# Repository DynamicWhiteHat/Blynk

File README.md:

# Blynk
A feature-rich LED controller

> [!NOTE]
> This board runs on [WLED firmware](https://kno.wled.ge/)

## Features:
- Powered by an ESP32 S3
- ICS-43434 microphone
- Plus line-in with ES7243
- Low-profile PIR for motion detection
- IR receiver with custom remote control
- BH1750 ambient light sensor
- Full RGBW CCT support
- Reverse polarity protection and automatic supply switching

## Image Gallery:
<table align="center">
  <tr>
    <td align="center">
      
    </td>
    <td align="center">
      
    </td>
  </tr>
  <tr>
    <td align="center" colspan="2">
      
    </td>
  </tr>
</table>

## Why I Designed This Project:
I began this project because I am getting a new large table built in my room and would love some LED lighting under it. I decided to make myself an LED controller with a lot of features. Most importantly, I wanted to have it be compatible with Alexa to match the other lights in my room. After a quick search, I found that the WLED firmware accomplishes all that I want: it is feature-rich, Alexa compatible, and supports custom ESP32 boards. And so, I embarked on a quest to make the most feature-packed LED controller to exist.

## Schematics And PCBs:
<table align="center">
  <tr>
    <td align="center" colspan="2">
      
    </td>
  </tr>
  <tr>
     <td align="center">
      
    </td>
    <td align="center">
      
    </td>
  </tr>
</table>

## Usage:
Follow the instructions on the [WLED getting started page](https://kno.wled.ge/basics/getting-started/) after assembling your PCB to get it running.

## BOM:
|Part                       |Quantity       |Price              |Link                                                                                  |                 |        |   |                                            |
|---------------------------|---------------|-------------------|--------------------------------------------------------------------------------------|-----------------------|--------------|---------|--------------------------------------------------|
|PCB+Stencil                |1              |$24.07             |JLCPCB Quote                                                                          |                       |              |         |                                                  |
|PCB Parts                  |1              |$56.25             |See Below                                                                             |                       |              |         |                                                  |
|LED Strip                  |1              |$6.96              |https://www.aliexpress.us/item/3256808756097464.html                                  |                       |              |         |                                                  |
|M2 Screws                  |1              |$5.22              |https://www.aliexpress.us/item/3256807092650644.html                                  |                       |              |         |                                                  |
|Power Supply               |1              |$13.94             |https://www.amazon.com/TOBWOLF-100V-240V-Transformer-Switching-Converter/dp/B0B1DGBVKB|                       |              |         |                                                  |
|PIR                        |1              |$3.48              |https://www.aliexpress.us/item/3256812509957711.html                                  |                       |              |         |                                                  |
|                           |Total          |$109.92            |                                                                                      |                       |              |         |                                                  |
|LCSC BOM                   |               |                   |                                                                                      |                       |              |         |                                                  |
|Description                |Quantity Needed|Mrf#               |Minimum Order Qty.                                                                    |Unit Price(USD)        |Ext.Price(USD)|LCSC#    |Product Link                                      |
|0.1uF                      |6              |CC0603KRX7R9BB104  |50                                                                                    |0.0186                 |0.93          |C14663   |https://www.lcsc.com/product-detail/C14663.html   |
|100K                       |1              |0603WAF1003T5E     |100                                                                                   |0.0068                 |0.68          |C25803   |https://www.lcsc.com/product-detail/C25803.html   |
|100R                       |3              |0603WAF1000T5E     |100                                                                                   |0.0222                 |2.22          |C22775   |https://www.lcsc.com/product-detail/C22775.html   |
|100nF                      |4              |CC0603KRX7R9BB104  |50                                                                                    |0.0186                 |0.93          |C14663   |https://www.lcsc.com/product-detail/C14663.html   |
|10K                        |8              |0603WAF1002T5E     |100                                                                                   |0.0085                 |0.85          |C25804   |https://www.lcsc.com/product-detail/C25804.html   |
|10uF                       |1              |CL10A106MA8NRNC    |20                                                                                    |0.0841                 |1.68          |C96446   |https://www.lcsc.com/product-detail/C96446.html   |
|150R                       |1              |0603WAF1500T5E     |100                                                                                   |0.0087                 |0.87          |C22808   |https://www.lcsc.com/product-detail/C22808.html   |
|1K                         |1              |0603WAF1001T5E     |100                                                                                   |0.0058                 |0.58          |C21190   |https://www.lcsc.com/product-detail/C21190.html   |
|1uF                        |10             |CL10A105KB8NNNC    |50                                                                                    |0.0275                 |1.38          |C15849   |https://www.lcsc.com/product-detail/C15849.html   |
|2.2uH                      |1              |CMH160808B2R2MT    |20                                                                                    |0.0324                 |0.65          |C394950  |https://www.lcsc.com/product-detail/C394950.html  |
|20K                        |1              |0603WAF2002T5E     |100                                                                                   |0.0052                 |0.52          |C4184    |https://www.lcsc.com/product-detail/C4184.html    |
|220R                       |5              |0603WAF2200T5E     |100                                                                                   |0.0086                 |0.86          |C22962   |https://www.lcsc.com/product-detail/C22962.html   |
|22uF                       |5              |CL10A226MQ8NRNC    |20                                                                                    |0.0313                 |0.63          |C59461   |https://www.lcsc.com/product-detail/C59461.html   |
|33.2K                      |1              |0603WAF3322T5E     |100                                                                                   |0.0034                 |0.34          |C23003   |https://www.lcsc.com/product-detail/C23003.html   |
|4.7K                       |3              |0603WAF4701T5E     |100                                                                                   |0.0118                 |1.18          |C23162   |https://www.lcsc.com/product-detail/C23162.html   |
|4.7uF                      |1              |CL10A475KO8NNNC    |10                                                                                    |0.0335                 |0.34          |C19666   |https://www.lcsc.com/product-detail/C19666.html   |
|47R                        |1              |0603WAF470JT5E     |100                                                                                   |0.0075                 |0.75          |C23182   |https://www.lcsc.com/product-detail/C23182.html   |
|5.1k                       |2              |0603WAF5101T5E     |100                                                                                   |0.0038                 |0.38          |C23186   |https://www.lcsc.com/product-detail/C23186.html   |
|750 mA                     |1              |BSMD0603-075-6V    |10                                                                                    |0.0672                 |0.67          |C914092  |https://www.lcsc.com/product-detail/C914092.html  |
|8A                         |1              |BSMD2920L-1000-24V |1                                                                                     |0.634                  |0.63          |C48392676|https://www.lcsc.com/product-detail/C48392676.html|
|AO3400A                    |6              |AO3400A            |10                                                                                    |0.0849                 |0.85          |C20917   |https://www.lcsc.com/product-detail/C20917.html   |
|AOD4184A                   |1              |AOD4184A           |5                                                                                     |0.3474                 |1.74          |C99124   |https://www.lcsc.com/product-detail/C99124.html   |
|ATtiny1616-S               |1              |ATTINY1616-SN      |1                                                                                     |2.9131                 |2.91          |C614136  |https://www.lcsc.com/product-detail/C614136.html  |
|AudioPlug3                 |1              |SJ1-3523N          |1                                                                                     |0.8493                 |0.85          |C20182914|https://www.lcsc.com/product-detail/C20182914.html|
|BH1750                     |1              |BH1750FVI-TR       |1                                                                                     |0.9687                 |0.97          |C78960   |https://www.lcsc.com/product-detail/C78960.html   |
|BLM15PX121SN1D             |2              |BLM15PX121SN1D11   |50                                                                                    |0.0097                 |0.49          |C882964  |https://www.lcsc.com/product-detail/C882964.html  |
|CR2032                     |1              |BS-07-A1BJ001      |5                                                                                     |0.379                  |1.9           |C2979167 |https://www.lcsc.com/product-detail/C2979167.html |
|D                          |1              |BSD3C051V          |10                                                                                    |0.0661                 |0.66          |C151996  |https://www.lcsc.com/product-detail/C151996.html  |
|ES7243                     |1              |ES7243E            |1                                                                                     |0.5557                 |0.56          |C2929446 |https://www.lcsc.com/product-detail/C2929446.html |
|ESP32-S3-WROOM-1           |1              |ESP32-S3-WROOM-1-N8|1                                                                                     |4.91                   |4.91          |C2913198 |https://www.lcsc.com/product-detail/C2913198.html |
|ICS-43434                  |1              |ICS-43434          |1                                                                                     |3.8207                 |3.82          |C5656610 |https://www.lcsc.com/product-detail/C5656610.html |
|LM5050-1                   |1              |LM5050MK-1/NOPB    |1                                                                                     |1.1867                 |1.19          |C129323  |https://www.lcsc.com/product-detail/C129323.html  |
|SMBJ15A                    |1              |SMBJ15A            |5                                                                                     |0.0539                 |0.27          |C19077569|https://www.lcsc.com/product-detail/C19077569.html|
|SS34                       |1              |SS34               |20                                                                                    |0.0352                 |0.7           |C8678    |https://www.lcsc.com/product-detail/C8678.html    |
|SW_Push                    |2              |TS-1088-AR02016    |10                                                                                    |0.0529                 |0.53          |C720477  |https://www.lcsc.com/product-detail/C720477.html  |
|SW_Push_45deg              |12             |TS-1088-AR02016    |20                                                                                    |0.0529                 |1.06          |C720477  |https://www.lcsc.com/product-detail/C720477.html  |
|Screw_Terminal_01x02       |1              |KF126-5.0-2P       |5                                                                                     |0.0844                 |0.42          |C474900  |https://www.lcsc.com/product-detail/C474900.html  |
|TPS563201                  |1              |TPS563201DDCR      |10                                                                                    |0.0769                 |0.77          |C116592  |https://www.lcsc.com/product-detail/C116592.html  |
|TSAL4400                   |1              |TSAL4400           |5                                                                                     |0.4254                 |2.13          |C94135   |https://www.lcsc.com/product-detail/C94135.html   |
|TSOP38238                  |1              |TSOP38238          |1                                                                                     |0.7752                 |0.78          |C141632  |https://www.lcsc.com/product-detail/C141632.html  |
|USBLC6-2P6                 |1              |USBLC6-2P6         |5                                                                                     |0.2787                 |1.39          |C15999   |https://www.lcsc.com/product-detail/C15999.html   |
|USB_C_Receptacle_USB2.0_16P|1              |TYPE-C-31-M-12     |5                                                                                     |0.1716                 |0.86          |C165948  |https://www.lcsc.com/product-detail/C165948.html  |
|                           |               |                   |                                                                                      |Subtotal:              |46.83         |         |                                                  |
|                           |               |                   |                                                                                      |Shipping:              |12.76         |         |                                                  |
|                           |               |                   |                                                                                      |Total (after discount):|$56.25        |         |                                                  |

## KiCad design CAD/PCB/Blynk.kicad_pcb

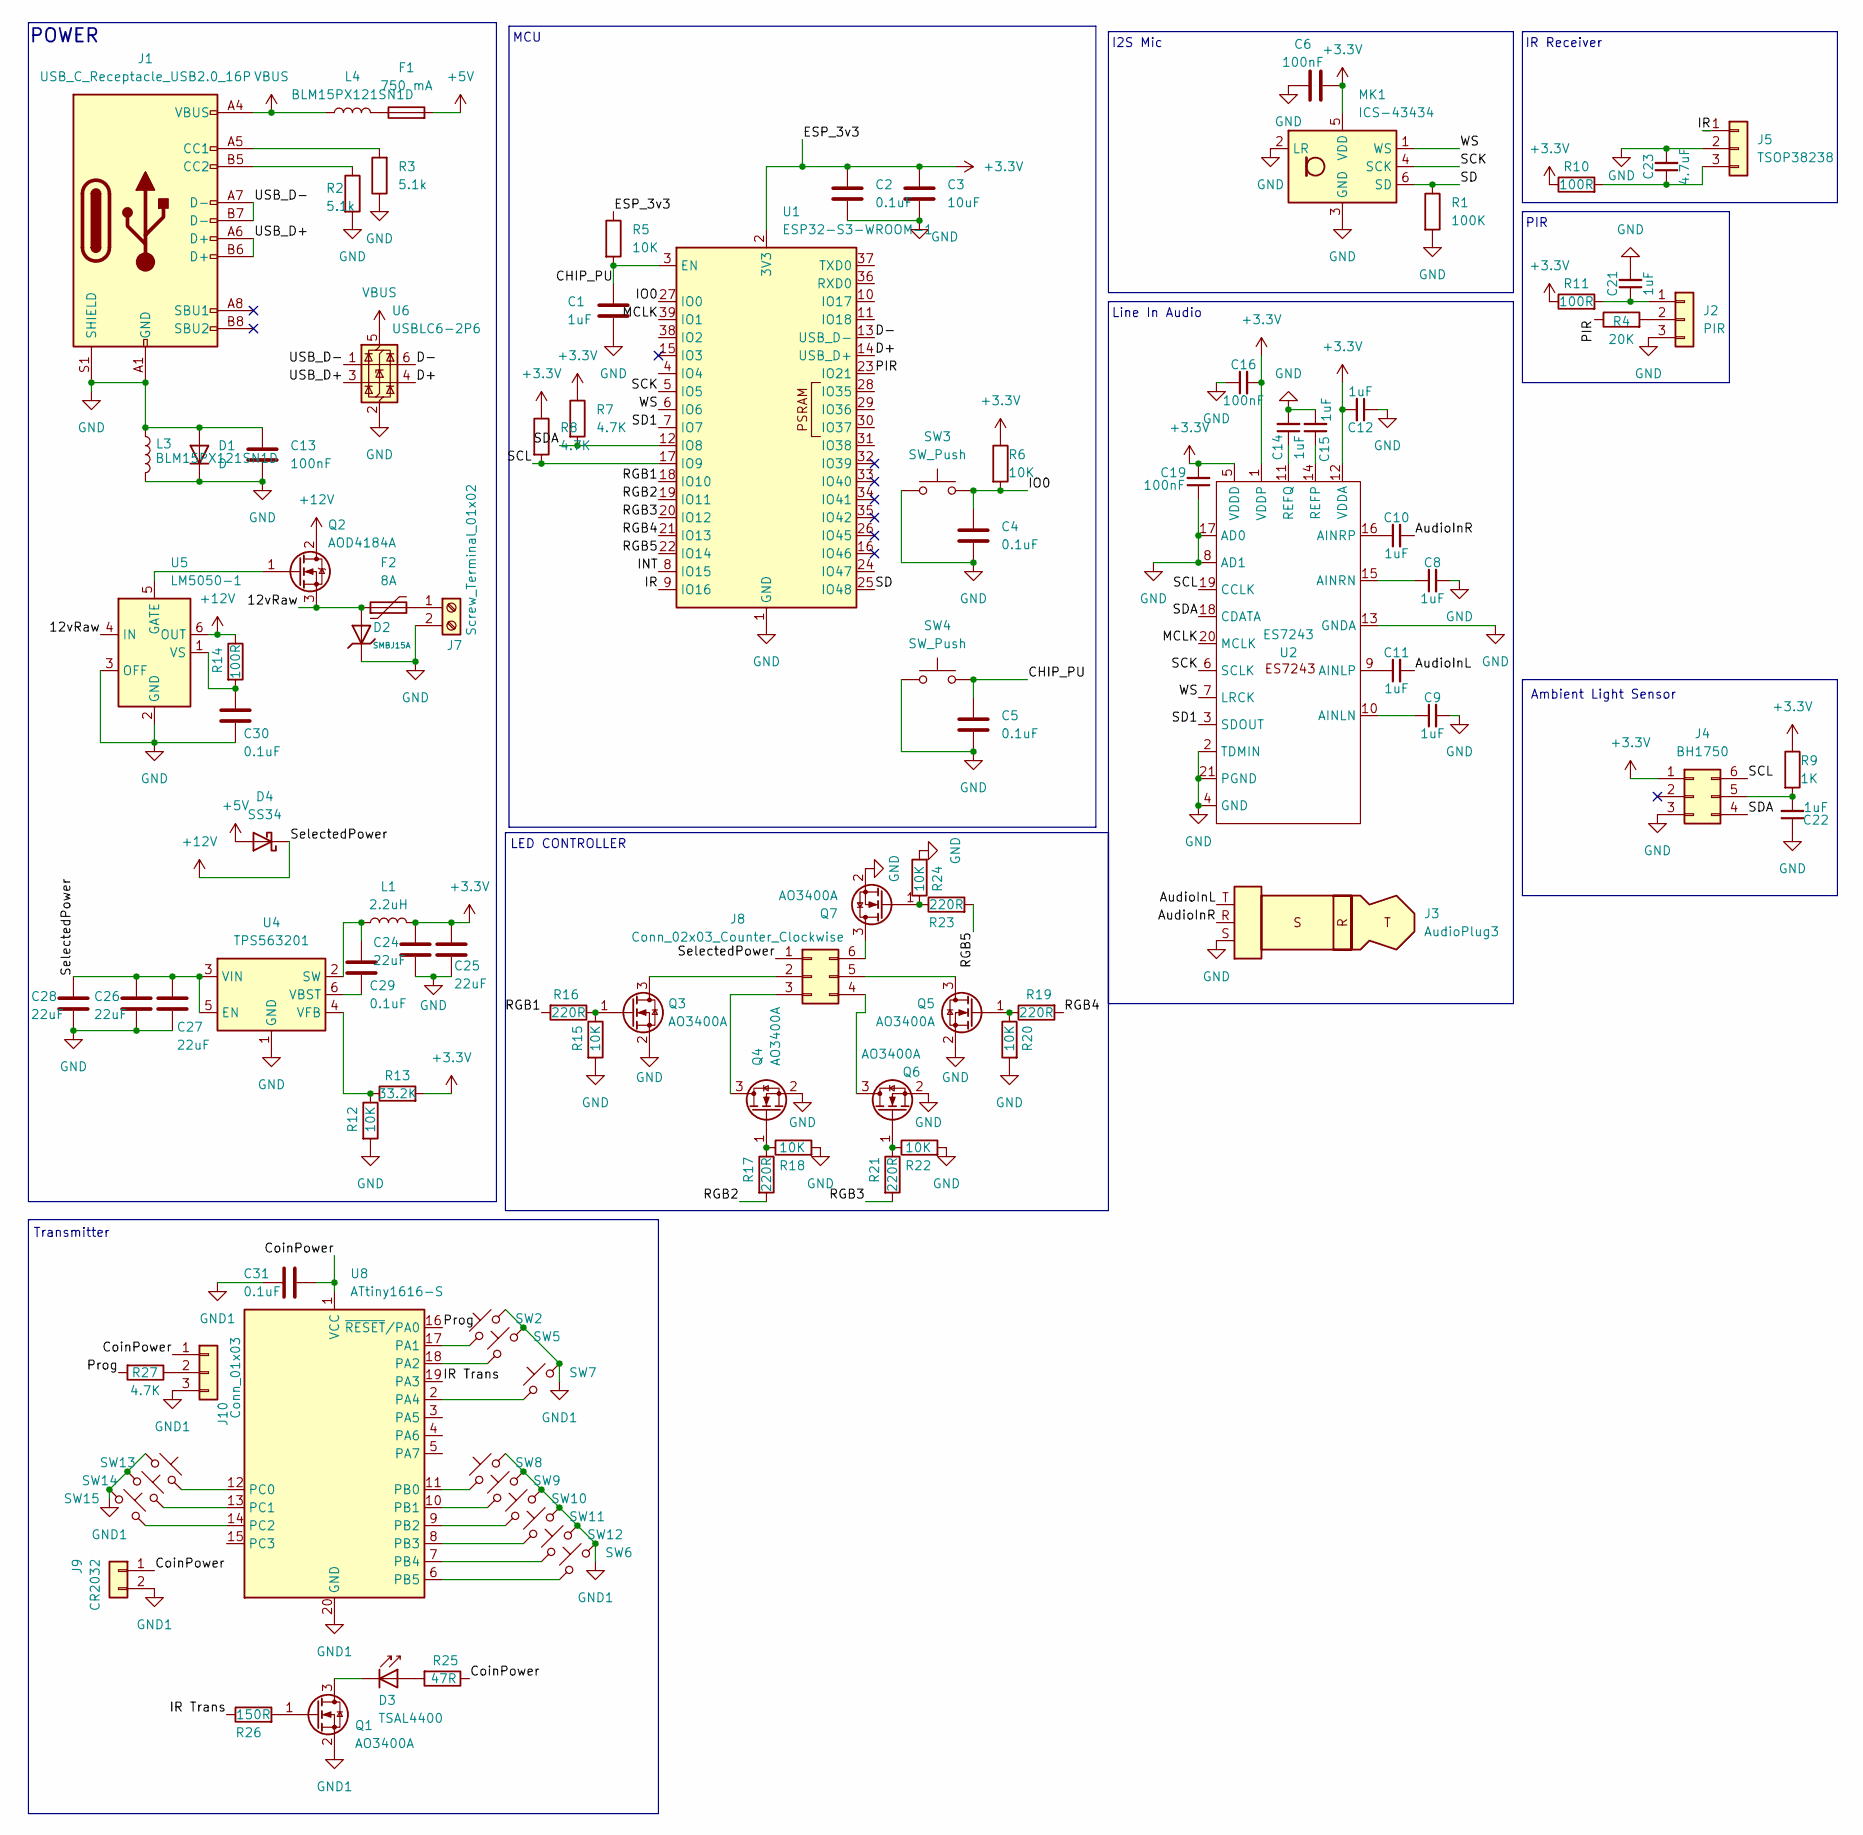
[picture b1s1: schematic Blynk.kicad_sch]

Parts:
C1, C8, C9, C10, C11, C12, C14, C15, C21, C22: 1uF; C_0603_1608Metric
C2, C4, C5, C29, C30, C31: 0.1uF; C_0603_1608Metric
C3: 10uF; C_0603_1608Metric
C6, C13, C16, C19: 100nF; C_0603_1608Metric
C23: 4.7uF; C_0603_1608Metric
C24, C25, C26, C27, C28: 22uF; C_0603_1608Metric
D1: D; D_SOD-323
D2: SMBJ15A; D_SMB; Part SMBJ15A; LCSC C19077569
D3: TSAL4400; LED_D3.0mm_IRBlack
D4: SS34; D_SMA
F1: 750 mA; Fuse_0603_1608Metric
F2: 8A; Fuse_2920_7451Metric
J1: USB_C_Receptacle_USB2.0_16P; USB_C_Receptacle_HRO_TYPE-C-31-M-12
J2: PIR; PinHeader_1x03_P2.54mm_Vertical
J3: AudioPlug3; Jack_3.5mm_CUI_SJ1-3523N_Horizontal
J4: BH1750; XDCR_BH1750FVI-TR
J5: TSOP38238; PinHeader_1x03_P2.54mm_Vertical
J7: Screw_Terminal_01x02; Altech_AK100_1x02_P5.00mm
J8: Conn_02x03_Counter_Clockwise; PinHeader_1x06_P2.54mm_Vertical
J9: CR2032; BatteryHolder_MYOUNG_BS-07-A1BJ001_CR2032
J10: Conn_01x03; PinHeader_1x03_P1.27mm_Vertical
L1: 2.2uH; L_0603_1608Metric
L3, L4: BLM15PX121SN1D; L_0402_1005Metric
MK1: ICS-43434; InvenSense_ICS-43434-6_3.5x2.65mm
Q1, Q3, Q4, Q5, Q6, Q7: AO3400A; SOT-23
Q2: AOD4184A; TO-252-2
R1: 100K; R_0603_1608Metric
R2, R3: 5.1k; R_0603_1608Metric
R4: 20K; R_0603_1608Metric
R5, R6, R12, R15, R18, R20, R22, R24: 10K; R_0603_1608Metric
R7, R8, R27: 4.7K; R_0603_1608Metric
R9: 1K; R_0603_1608Metric
R10, R11, R14: 100R; R_0603_1608Metric
R13: 33.2K; R_0603_1608Metric
R16, R17, R19, R21, R23: 220R; R_0603_1608Metric
R25: 47R; R_0603_1608Metric
R26: 150R; R_0603_1608Metric
SW2, SW5, SW6, SW7, SW8, SW9, SW10, SW11, SW12, SW13, SW14, SW15: SW_Push_45deg; SW_TS-1088-AR02016
SW3, SW4: SW_Push; SW_TS-1088-AR02016
U1: ESP32-S3-WROOM-1
U2: ES7243; QFN-20-1EP_3x3mm_P0.4mm_EP1.65x1.65mm
U4: TPS563201; SOT-23-6
U5: LM5050-1; TSOT-23-6
U6: USBLC6-2P6; SOT-666
U8: ATtiny1616-S; SOIC-20W_7.5x12.8mm_P1.27mm

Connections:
+3.3V: C2.1, C3.1, C6.2, C12.2, C16.2, C19.2, C24.1, C25.1, J4.1, L1.2, MK1.5 (VDD), R5.1, R6.1, R7.1, R8.1, R9.1, R10.1, R11.1, R13.2, U1.2 (3V3), U2.1 (VDDP), U2.5 (VDDD), U2.12 (VDDA)
+5V: D4.2 (A), F1.2
+12V: C26.1, C27.1, C28.1, D4.1 (K), J8.1, Q2.2 (D), R14.1, U4.3 (VIN), U4.5 (EN), U5.6 (OUT)
/12vRaw: D2.2, F2.1, Q2.3 (S), U5.4 (IN)
/AudioInL: C11.2, J3.T
/AudioInR: C10.2, J3.R
/CHIP_PU: C1.1, C5.1, R5.2, SW4.2, U1.3 (EN)
/CoinPower: C31.1, J9.1, J10.1, R25.1, U8.1 (VCC)
/D+: U1.14 (USB_D+), U6.4 (I/O2)
/D-: U1.13 (USB_D-), U6.6 (I/O1)
/INT: U1.8 (IO15)
/IO0: C4.1, R6.2, SW3.2, U1.27 (IO0)
/IR: J5.1, U1.9 (IO16)
/IR Trans: R26.1, U8.19 (PA3)
/MCLK: U1.39 (IO1), U2.20 (MCLK)
/PIR: R4.1, U1.23 (IO21)
/Prog: R27.2, U8.16 (~RESET/PA0)
/RGB1: R16.2, U1.18 (IO10)
/RGB2: R17.2, U1.19 (IO11)
/RGB3: R21.2, U1.20 (IO12)
/RGB4: R19.2, U1.21 (IO13)
/RGB5: R23.2, U1.22 (IO14)
/SCK: MK1.4 (SCK), U1.5 (IO5), U2.6 (SCLK)
/SCL: J4.6, R8.2, U1.17 (IO9), U2.19 (CCLK)
/SD: MK1.6 (SD), R1.1, U1.25 (IO48)
/SD1: U1.7 (IO7), U2.3 (SDOUT)
/SDA: J4.4, R7.2, U1.12 (IO8), U2.18 (CDATA)
/USB_D+: J1.A6 (D+), J1.B6 (D+), U6.3 (I/O2)
/USB_D-: J1.A7 (D-), J1.B7 (D-), U6.1 (I/O1)
/WS: MK1.1 (WS), U1.6 (IO6), U2.7 (LRCK)
GND: C1.2, C2.2, C3.2, C4.2, C5.2, C6.1, C8.2, C9.2, C12.1, C13.1, C13.2, C14.2, C15.2, C16.1, C19.1, C21.2, C22.1, C23.2, C24.2, C25.2, C26.2, C27.2, C28.2, C30.2, D1.1 (K), D1.2 (A), D2.1, J1.A1 (GND), J1.A12 (GND), J1.B1 (GND), J1.B12 (GND), J1.S1 (SHIELD), J2.3, J3.S, J4.3, J5.2, J7.2, L3.1, L3.2, MK1.2 (LR), MK1.3 (GND), Q3.2 (S), Q4.2 (S), Q5.2 (S), Q6.2 (S), Q7.2 (S), R1.2, R2.2, R3.1, R12.2, R15.2, R18.2, R20.2, R22.2, R24.2, SW3.1, SW4.1, U1.1 (GND), U1.40 (GND), U1.41 (GND), U2.2 (TDMIN), U2.4 (GND), U2.8 (AD1), U2.13 (GNDA), U2.17 (AD0), U2.21 (PGND), U4.1 (GND), U5.2 (GND), U5.3 (OFF), U6.2 (GND)
GND1: C31.2, J9.2, J10.3, Q1.2 (S), SW2.2, SW5.2, SW6.2, SW7.2, SW8.2, SW9.2, SW10.2, SW11.2, SW12.2, SW13.2, SW14.2, SW15.2, U8.20 (GND)
unnamed: D3.2 (A), R25.2
unnamed: D3.1 (K), Q1.3 (D)
unnamed: F1.1, L4.2
unnamed: J1.A5 (CC1), R3.2
unnamed: J1.B5 (CC2), R2.1
unnamed: C21.1, J2.1, R11.2
unnamed: J2.2, R4.2
unnamed: C22.2, J4.5, R9.2
unnamed: C23.1, J5.3, R10.2
unnamed: F2.2, J7.1
unnamed: J8.2, Q3.3 (D)
unnamed: J8.3, Q4.3 (D)
unnamed: J8.4, Q6.3 (D)
unnamed: J8.5, Q5.3 (D)
unnamed: J8.6, Q7.3 (D)
unnamed: J10.2, R27.1
unnamed: Q1.1 (G), R26.2
unnamed: Q2.1 (G), U5.5 (GATE)
unnamed: Q3.1 (G), R15.1, R16.1
unnamed: Q4.1 (G), R17.1, R18.1
unnamed: Q5.1 (G), R19.1, R20.1
unnamed: Q6.1 (G), R21.1, R22.1
unnamed: Q7.1 (G), R23.1, R24.1
unnamed: C9.1, U2.10 (AINLN)
unnamed: C11.1, U2.9 (AINLP)
unnamed: C8.1, U2.15 (AINRN)
unnamed: C10.1, U2.16 (AINRP)
unnamed: C15.1, U2.14 (REFP)
unnamed: C14.1, U2.11 (REFQ)
unnamed: C29.1, L1.1, U4.2 (SW)
unnamed: C29.2, U4.6 (VBST)
unnamed: R12.1, R13.1, U4.4 (VFB)
unnamed: C30.1, R14.2, U5.1 (VS)
unnamed: SW2.1, U8.17 (PA1)
unnamed: SW5.1, U8.18 (PA2)
unnamed: SW7.1, U8.2 (PA4)
unnamed: SW8.1, U8.11 (PB0)
unnamed: SW9.1, U8.10 (PB1)
unnamed: SW10.1, U8.9 (PB2)
unnamed: SW11.1, U8.8 (PB3)
unnamed: SW12.1, U8.7 (PB4)
unnamed: SW6.1, U8.6 (PB5)
unnamed: SW13.1, U8.12 (PC0)
unnamed: SW14.1, U8.13 (PC1)
unnamed: SW15.1, U8.14 (PC2)
VBUS: J1.A4 (VBUS), J1.A9 (VBUS), J1.B4 (VBUS), J1.B9 (VBUS), L4.1, U6.5 (VBUS)

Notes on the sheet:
Ambient Light Sensor
LED CONTROLLER
Line In Audio
MCU
POWER
Transmitter
PIR
I2S Mic
IR Receiver

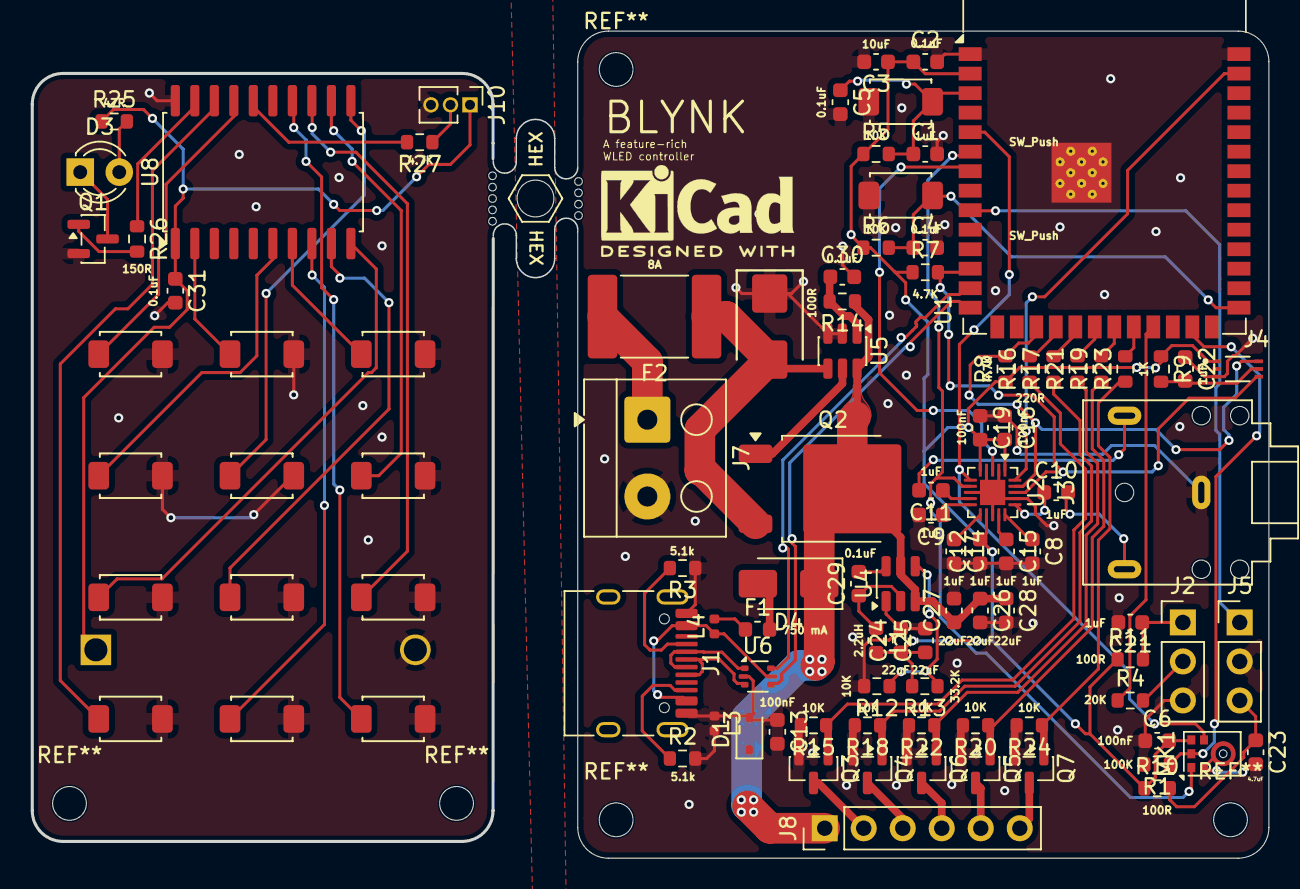
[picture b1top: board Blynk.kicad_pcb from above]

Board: 2 copper layers, 80.5 x 53.8 mm, 101 parts (1 on the bottom side), 77 nets.

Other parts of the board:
MB5: 5.5mm; mousebites_5p5mm_easysnap

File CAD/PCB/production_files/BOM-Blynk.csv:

Comment,Designator,Footprint,LCSC,Quantity
0.1uF,"C2,C29,C30,C31,C4,C5",C_0603_1608Metric,C14663,6
100K,R1,R_0603_1608Metric,C25803,1
100R,"R10,R11,R14",R_0603_1608Metric,C22775,3
100nF,"C13,C16,C19,C6",C_0603_1608Metric,C14663,4
10K,"R12,R15,R18,R20,R22,R24,R5,R6",R_0603_1608Metric,C25804,8
10uF,C3,C_0603_1608Metric,C96446,1
150R,R26,R_0603_1608Metric,C22808,1
1K,R9,R_0603_1608Metric,C21190,1
1uF,"C1,C10,C11,C12,C14,C15,C21,C22,C8,C9",C_0603_1608Metric,C15849,10
2.2uH,L1,L_0603_1608Metric,C394950,1
20K,R4,R_0603_1608Metric,C4184,1
220R,"R16,R17,R19,R21,R23",R_0603_1608Metric,C22962,5
22uF,"C24,C25,C26,C27,C28",C_0603_1608Metric,C59461,5
33.2K,R13,R_0603_1608Metric,C23003,1
4.7K,"R27,R7,R8",R_0603_1608Metric,C23162,3
4.7uF,C23,C_0603_1608Metric,C19666,1
47R,R25,R_0603_1608Metric,C23182,1
5.1k,"R2,R3",R_0603_1608Metric,C23186,2
750 mA,F1,Fuse_0603_1608Metric,C914092,1
8A,F2,Fuse_2920_7451Metric,C48392676,1
AO3400A,"Q1,Q3,Q4,Q5,Q6,Q7",SOT-23,C20917,6
AOD4184A,Q2,TO-252-2,C99124,1
ATtiny1616-S,U8,SOIC-20W_7.5x12.8mm_P1.27mm,C614136,1
AudioPlug3,J3,Jack_3.5mm_CUI_SJ1-3523N_Horizontal,C20182914,1
BH1750,J4,XDCR_BH1750FVI-TR,C78960,1
BLM15PX121SN1D,"L3,L4",L_0402_1005Metric,C882964,2
CR2032,J9,BatteryHolder_MYOUNG_BS-07-A1BJ001_CR2032,C2979167,1
D,D1,D_SOD-323,C151996,1
ES7243,U2,QFN-20-1EP_3x3mm_P0.4mm_EP1.65x1.65mm,C2929446,1
ESP32-S3-WROOM-1,U1,ESP32-S3-WROOM-1,C2913198,1
ICS-43434,MK1,InvenSense_ICS-43434-6_3.5x2.65mm,C5656610,1
LM5050-1,U5,TSOT-23-6,C129323,1
SMBJ15A,D2,D_SMB,C19077569,1
SS34,D4,D_SMA,C8678,1
SW_Push,"SW3,SW4",SW_TS-1088-AR02016,C720477,2
SW_Push_45deg,"SW10,SW11,SW12,SW13,SW14,SW15,SW2,SW5,SW6,SW7,SW8,SW9",SW_TS-1088-AR02016,C720477,12
Screw_Terminal_01x02,J7,Altech_AK100_1x02_P5.00mm,C474900,1
TPS563201,U4,SOT-23-6,C116592,1
TSAL4400,D3,LED_D3.0mm_IRBlack,C94135,1
TSOP38238,J5,PinHeader_1x03_P2.54mm_Vertical,C141632,1
USBLC6-2P6,U6,SOT-666,C15999,1
USB_C_Receptacle_USB2.0_16P,J1,USB_C_Receptacle_HRO_TYPE-C-31-M-12,C165948,1
Conn_01x03,J10,PinHeader_1x03_P1.27mm_Vertical,,1
PIR,J2,PinHeader_1x03_P2.54mm_Vertical,,1
Conn_02x03_Counter_Clockwise,J8,PinHeader_1x06_P2.54mm_Vertical,,1
